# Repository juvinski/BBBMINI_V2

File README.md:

This project is an updated version of the BBBMINI from Mirko Denecke - https://github.com/mirkix/BBBMINI/

This is a cape for Beaglebone Black or Green:

The main differences between BBBMini and BBBMini V2:
* IMU updated to the ICM-20948.
* 3 Serial ports - Telemetry, GPS and Sonar, Lidar or other serial sensor.
* PWM Buzzer with transistor included on the board.
* CAN Bus using breakout sensor board - TJA 1051.
* PullUP resitors for the I2C bus.
* Power Button pinheader.
* ABC leds.
* GPIO pins for relay pins.
* Debian Buster
* Realtime Kernel 5.10.
* Ardupilot 4.2.

# License

<br /><span xmlns:dct="http://purl.org/dc/terms/" property="dct:title">BBBmini V2</span> by <a xmlns:cc="http://creativecommons.org/ns#" href="https://github.com/juvinski" property="cc:attributionName" rel="cc:attributionURL">Vinicius Juvinski</a> is licensed under a <a rel="license" href="http://creativecommons.org/licenses/by-sa/4.0/">Creative Commons Attribution-ShareAlike 4.0 International License</a>.

UNLESS OTHERWISE MUTUALLY AGREED TO BY THE PARTIES IN WRITING, LICENSOR OFFERS THE WORK AS-IS AND MAKES NO REPRESENTATIONS OR WARRANTIES OF ANY KIND CONCERNING THE WORK, EXPRESS, IMPLIED, STATUTORY OR OTHERWISE, INCLUDING, WITHOUT LIMITATION, WARRANTIES OF TITLE, MERCHANTABILITY, FITNESS FOR A PARTICULAR PURPOSE, NONINFRINGEMENT, OR THE ABSENCE OF LATENT OR OTHER DEFECTS, ACCURACY, OR THE PRESENCE OF ABSENCE OF ERRORS, WHETHER OR NOT DISCOVERABLE. SOME JURISDICTIONS DO NOT ALLOW THE EXCLUSION OF IMPLIED WARRANTIES, SO SUCH EXCLUSION MAY NOT APPLY TO YOU. EXCEPT TO THE EXTENT REQUIRED BY APPLICABLE LAW, IN NO EVENT WILL LICENSOR BE LIABLE TO YOU ON ANY LEGAL THEORY FOR ANY SPECIAL, INCIDENTAL, CONSEQUENTIAL, PUNITIVE OR EXEMPLARY DAMAGES ARISING OUT OF THIS LICENSE OR THE USE OF THE WORK, EVEN IF LICENSOR HAS BEEN ADVISED OF THE POSSIBILITY OF SUCH DAMAGES.

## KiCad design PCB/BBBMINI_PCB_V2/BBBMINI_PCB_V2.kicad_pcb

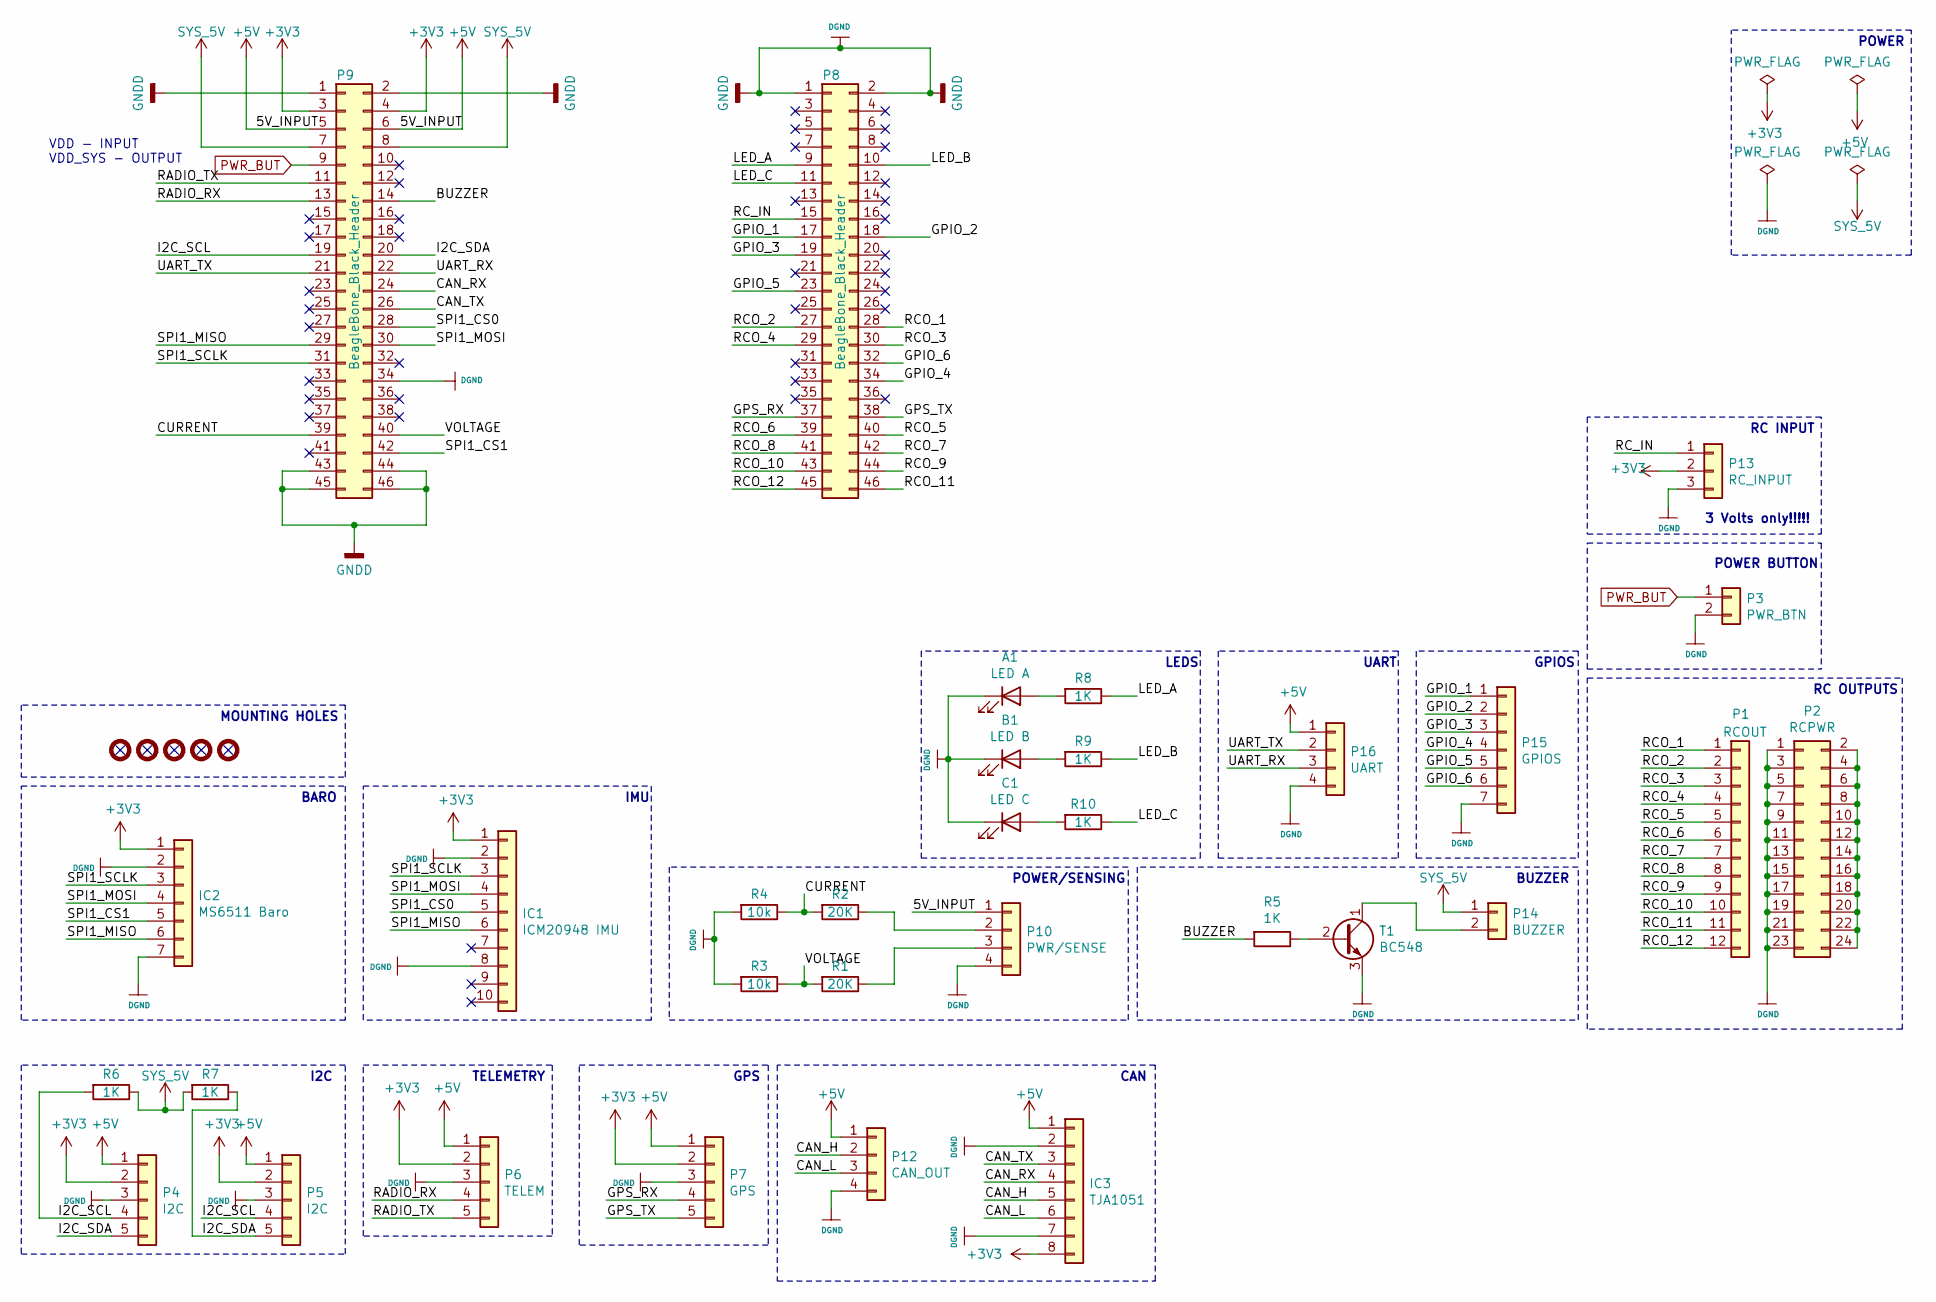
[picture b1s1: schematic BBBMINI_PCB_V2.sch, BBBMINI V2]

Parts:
A1: LED A; LED_D1.8mm_W3.3mm_H2.4mm
B1: LED B; LED_D1.8mm_W3.3mm_H2.4mm
C1: LED C; LED_D1.8mm_W3.3mm_H2.4mm
IC1: ICM20948 IMU; PinHeader_1x10_P2.54mm_Vertical
IC2: MS6511 Baro; PinHeader_1x07_P2.54mm_Vertical
IC3: TJA1051; PinHeader_1x08_P2.54mm_Vertical
M1: MOUNTING-HOLE; MountingHole_2.2mm_M2_Pad
M2, M3, M4, M5: M; MountingHole_2.2mm_M2_Pad
P1: RCOUT; PinHeader_1x12_P2.54mm_Vertical
P2: RCPWR; PinHeader_2x12_P2.54mm_Vertical
P3: PWR_BTN; PinHeader_1x02_P2.54mm_Vertical
P4, P5: I2C; PinHeader_1x05_P2.54mm_Vertical
P6: TELEM; PinHeader_1x05_P2.54mm_Vertical
P7: GPS; PinHeader_1x05_P2.54mm_Vertical
P8, P9: BeagleBone_Black_Header; Socket_BeagleBone_Black
P10: PWR/SENSE; PinHeader_1x04_P2.54mm_Vertical
P12: CAN_OUT; PinHeader_1x04_P2.54mm_Vertical
P13: RC_INPUT; PinHeader_1x03_P2.54mm_Vertical
P14: BUZZER; PinHeader_1x02_P2.54mm_Vertical
P15: GPIOS; PinHeader_1x07_P2.54mm_Vertical
P16: UART; PinHeader_1x04_P2.54mm_Vertical
R1, R2: 20K; R_Axial_DIN0207_L6.3mm_D2.5mm_P7.62mm_Horizontal
R3, R4: 10k; R_Axial_DIN0207_L6.3mm_D2.5mm_P7.62mm_Horizontal
R5: 1K; R_Axial_DIN0207_L6.3mm_D2.5mm_P7.62mm_Horizontal
R6, R7, R8, R9, R10: 1K; R_Axial_DIN0207_L6.3mm_D2.5mm_P2.54mm_Vertical
T1: BC548; TO-92_Inline

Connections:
+3V3: IC1.1, IC2.1, IC3.8, P4.2, P5.2, P6.2, P7.2, P9.3, P9.4, P13.2
+5V: IC3.1, P4.1, P5.1, P6.1, P7.1, P9.5, P9.6, P10.1, P12.1, P16.1
/BUZZER: P9.14, R5.2
/CAN_H: IC3.5, P12.2
/CAN_L: IC3.6, P12.3
/CAN_RX: IC3.4, P9.24
/CAN_TX: IC3.3, P9.26
/CURRENT: P9.39, R2.2, R4.1
/GPIO_1: P8.17, P15.1
/GPIO_2: P8.18, P15.2
/GPIO_3: P8.19, P15.3
/GPIO_4: P8.34, P15.4
/GPIO_5: P8.23, P15.5
/GPIO_6: P8.32, P15.6
/GPS_RX: P7.4, P8.37
/GPS_TX: P7.5, P8.38
/I2C_SCL: P4.4, P5.4, P9.19, R6.2
/I2C_SDA: P4.5, P5.5, P9.20, R7.1
/LED_A: P8.9, R8.1
/LED_B: P8.10, R9.1
/LED_C: P8.11, R10.1
/RADIO_RX: P6.4, P9.13
/RADIO_TX: P6.5, P9.11
/RCO_1: P1.1, P8.28
/RCO_2: P1.2, P8.27
/RCO_3: P1.3, P8.30
/RCO_4: P1.4, P8.29
/RCO_5: P1.5, P8.40
/RCO_6: P1.6, P8.39
/RCO_7: P1.7, P8.42
/RCO_8: P1.8, P8.41
/RCO_9: P1.9, P8.44
/RCO_10: P1.10, P8.43
/RCO_11: P1.11, P8.46
/RCO_12: P1.12, P8.45
/RC_IN: P8.15, P13.1
/SPI1_CS0: IC1.5, P9.28
/SPI1_CS1: IC2.5, P9.42
/SPI1_MISO: IC1.6, IC2.6, P9.29
/SPI1_MOSI: IC1.4, IC2.4, P9.30
/SPI1_SCLK: IC1.3, IC2.3, P9.31
/UART_RX: P9.22, P16.3
/UART_TX: P9.21, P16.2
/VOLTAGE: P9.40, R1.2, R3.1
DGND: A1.1 (K), B1.1 (K), C1.1 (K), IC1.2, IC1.8, IC2.2, IC2.7, IC3.2, IC3.7, P2.1, P2.3, P2.5, P2.7, P2.9, P2.11, P2.13, P2.15, P2.17, P2.19, P2.21, P2.23, P3.2, P4.3, P5.3, P6.3, P7.3, P8.1, P8.2, P9.1, P9.2, P9.34, P9.43, P9.44, P9.45, P9.46, P10.4, P12.4, P13.3, P15.7, P16.4, R3.2, R4.2, T1.3 (E)
unnamed: A1.2 (A), R8.2
unnamed: B1.2 (A), R9.2
unnamed: C1.2 (A), R10.2
unnamed: P2.2, P2.4, P2.6, P2.8, P2.10, P2.12, P2.14, P2.16, P2.18, P2.20, P2.22, P2.24
unnamed: P10.2, R2.1
unnamed: P10.3, R1.1
unnamed: P14.2, T1.1 (C)
unnamed: R5.1, T1.2 (B)
PWR_BUT: P3.1, P9.9
SYS_5V: P9.7, P9.8, P14.1, R6.1, R7.2

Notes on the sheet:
VDD - INPUT VDD_SYS - OUTPUT
RC OUTPUTS
POWER BUTTON
I2C
TELEMETRY
GPS
BARO
POWER
IMU
CAN
POWER/SENSING
RC INPUT
3 Volts only!!!!!
BUZZER
GPIOS
UART
MOUNTING HOLES
LEDS

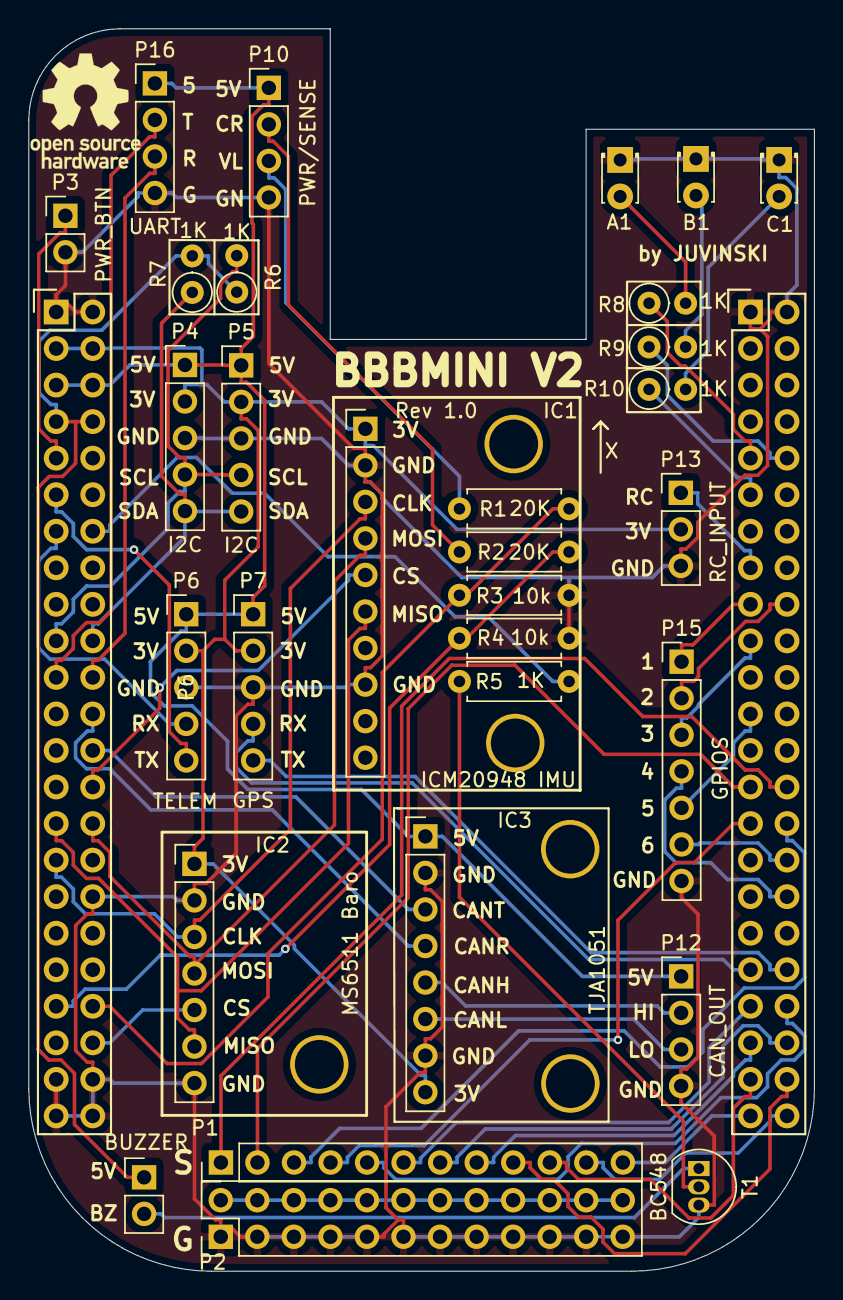
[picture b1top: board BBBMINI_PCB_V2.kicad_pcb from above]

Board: 2 copper layers, 54.6 x 86.4 mm, 37 parts (0 on the bottom side), 55 nets.

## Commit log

2022-05-11 Updated version
2022-05-24 Creation of updated version of the bbbmini dts
2022-05-24 Update on the software instruction to compile the dts for BBBMini
